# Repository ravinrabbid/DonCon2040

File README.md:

# DonCon2040 - A RP2040 based Taiko no Tatsujin arcade controller

DonCon2040 is a firmware (and by extension a PCB) for DIY Taiko no Tatsujin arcade style drum controllers.

It is pretty much tailored to this specific use case, if you are looking for something universal, ready-to-flash and on-the-fly configurable I'd recommend to have a look at more generic approaches like [GP2040-CE](https://github.com/OpenStickCommunity/GP2040-CE). If you however want build something more specialized or custom, feel free to use this project as a base, it is designed to be somewhat modular and should be easy remodel. See [DivaCon2040](https://github.com/ravinrabbid/DivaCon2040) for an example on how this could look like.
If you have any questions about the project in general or need hints how to build this thing, feel free to open a [discussion](https://github.com/ravinrabbid/DonCon2040/discussions) anytime!

## Features

- Various controller emulations
  - HORI PS4-095 Taiko Drum for Playstation 4 (will work on PS4, see [PS4 Authentication](#ps4-authentication) for details)
  - HORI NSW-079 Taiko Drum for Switch (compatible with Taiko no Tatsujin Rhythm Festival / Drum'n'Fun on Switch)
  - Bandai NC-110 Taiko Drum for Wii (needs to be connected to Wii Remote, see [Wii Support](#wii-support))
  - Namco NPC-107 Taiko Drum for Playstation 2 (needs to be connected to PS2 controller port, see [PS2 Support](#ps2-support))
  - Dualshock 4 (Only for PC/Steam, will not work on an actual PS4!)
  - Dualshock 3
  - Switch Pro Controller
  - XInput
  - XInput Analog (Compatible with [TaikoArcadeLoader](https://github.com/esuo1198/TaikoArcadeLoader) analog input)
  - Keyboard (Mapping: 'DFJK' / 'CBN,')
  - MIDI
  - Debug mode (will output current state via USB serial and allow direct flashing)
- Additional buttons via external i2c GPIO expander
- Basic configuration via on-screen menu on attached OLED screen
- Single WS2812 LED for trigger feedback
- Drumroll counter on display

## Building

I highly recommend to build the firmware yourself so you can make adjustments in `include/GlobalConfiguration.h` to match your specific controller build.
You can still use the [binary release](https://github.com/ravinrabbid/DonCon2040/releases) which is pre-configured for the [DonConIO](/pcb/DonConIO).

### VSCode (Windows, Linux, MacOS)

Install [VSCode](https://code.visualstudio.com/) and get the [Raspberry Pi Pico](https://marketplace.visualstudio.com/items?itemName=raspberry-pi.raspberry-pi-pico) extension. From the extension choose 'Import Project' and select the folder where you've checked out this repository, then use 'Compile Project'.

### CLI

See [pico-sdk readme](https://github.com/raspberrypi/pico-sdk/blob/master/README.md#quick-start-your-own-project) for a list of pre-requisites.

Use the environment variables `PICO_SDK_PATH` to use a local pico-sdk, and `PICO_BOARD` to select another target board.
By default the pico-sdk will be fetched from Github and the target board will be "pico".

For DonConIOmini with RP2040:

```sh
cmake -B build -DPICO_BOARD="waveshare_rp2040_zero"
cmake --build build
```

For DonConIOmini with RP2350:

```sh
cmake -B build -DPICO_BOARD="waveshare_rp2350_zero"
cmake --build build
```

For legacy DonConIO:

```sh
cmake -B build -DPICO_BOARD="seeed_xiao_rp2040"
cmake --build build
```

## Configuration

Few things which you probably want to change more regularly can be changed using an on-screen menu on the attached OLED display, hold both Start and Select for 2 seconds to enter the menu:

- Controller emulation mode
- LED brightness
- Trigger thresholds
- Hold Time
- Double Trigger Mode and Thresholds
- Enter BOOTSEL mode for firmware flashing

Those settings are persisted to flash memory if you choose 'Save' when exiting the Menu and will survive power cycles.

Defaults and everything else are compiled statically into the firmware. You can find everything in `include/GlobalConfiguration.h`. This covers default controller emulation mode, i2c pins, external ADC configuration, addresses and speed, default trigger thresholds, scale and debounce delay, button mapping, LED colors and brightness.

### Debounce Delay / Hold Time

The debounce delay also implicitly serves as the hold time of the input after a hit. On some platforms inputs won't be registered properly if this time is too short. For example Taiko no Tatsujin on Switch needs at least 25 milliseconds.

If you notice dropped inputs even if the controller signals a hit on the LED/Display, try to increase this value.

### Double Trigger (Large Notes)

Home versions of Taiko no Tatsujin give higher scores for large notes when both sides are hit simultaneously. In contrast, arcade versions will only need a normal hit (or sometimes a harder hit). To emulate this behavior, the following modes are offered:

- **Off**: Hit both sides to score large notes.
- **Threshold**: Automatically trigger both sides if a hit is stronger than the configured double hit threshold.
- **Always**: A hit on one side will always trigger the other side as well.

### PS4 Authentication

The PS4 needs a controller to sign a cryptographic challenge every few seconds, otherwise it will stop working after around 8 minutes after plugging in. For the Taiko no Tatsujin games this is somewhat bearable, since you can re-plug the controller before starting each song to avoid running into the timeout during gameplay. Still, this is annoying.

DonCon2040 can sign those challenges, but you will need to obtain some data from an original DS4 and compile it into the firmware. You will need a serial, signature and private key file. I can't and won't help you how to obtain those, you'll need to figure this out yourself.

To build the firmware run `scripts/generateAuthConfig.py` in the folder where you placed the required files. Copy the resulting `PS4AuthConfiguration.h` to the `include` directory, replacing the existing header. Then build the firmware as described in [Building](#building).

Signing the challenge will block the second core of the RP2040 for 2-3 seconds, so the display, external controller and LED will appear stuck from time to time. Input handling of the drum is unaffected.
On the RP2350 SHA256 is hardware accelerated, so signing time is reduced to about 1 second.

### Wii Support

To use the DonCon2040 with the Wii, it needs to be connected to the Wii Remote's extension port. This is only supported on boards exposing two I²C interfaces (i.e. the Waveshare RP2040/RP2350-Zero on the DonConIOmini).

See [the consolemods.org wiki](https://consolemods.org/wiki/Wii:Connector_Pinouts#Wii_Remote_Extension_Controller) for the pinout of the Wii Remote expansion port.
In the default configuration connect *SDA* to pin 0 and *SCL* to pin 1 of the RP2040/RP2350-Zero. Bridge *Sense* and *VCC* of the Wii Remote.

Since the Wii Remote is battery powered and the DonCon2040 needs to be powered externally because the Wii Remote does not provide enough power on the extension port,
I highly recommend to isolate the I²C bus (e.g. using an ISO1540 or ISO1640 I²C isolator).
While it does work when connecting the I²C signals directly, there is no guarantee there won't be any damage to the Wii Remote, its batteries or the DonCon2040 in the long run.
At least **DO NOT** connect both *VCC*s to avoid feeding power to the Wii Remote through the expansion port directly.

There is no dedicated mode for Wii support, it will be active in addition to the USB mode if `proprietary_device_config` is configured for Wii in `include/GlobalConfiguration.h`.

### PS2 Support

To use the DonCon2040 with the PS2, it needs to be connected to the PS2's controller port. This needs five consecutive GPIO pins on the RP2040/RP2350. The DonCon2040 still needs to be powered externally.

See [the consolemods.org wiki](https://consolemods.org/wiki/PS1:Connector_Pinouts#Controller_and_memory_card) for the pinout of the PS2 controller port.
The order of the signals lines is: Data, Command, Attention, Clock, Acknowledge.
In the default configuration, the base GPIO pin is 4, so the connection is as follows:

```txt
PS2 Controller Port     DonCon2040
----------------------------------
[1] (Data)          <-- GPIO4
[2] (Command)       --> GPIO5
[3] -
[4] GND             --- GND
[5] -
[6] (Attention)     --> GPIO6
[7] (Clock)         --> GPIO7
[8] -
[9] (Attention)     <-- GPIO8
```

There is no dedicated mode for PS2 support, it will be active in addition to the USB mode if `proprietary_device_config` is configured for PS2 in `include/GlobalConfiguration.h`.

## Hardware

### IO Board

The [DonConIOmini](/pcb/DonConIOmini) board in the pcb subfolder is designed to be close to the original arcade hardware. It hosts a Waveshare RP2040-Zero and provides signal conditioning for Sensatec GSS-4S* piezo impact sensors. See its [README](/pcb/DonConIOmini/README.md) for details.

If you don't want to use this board, the firmware should be usable on most RP2040/RP2350 boards with appropriate configuration. You may also use a more simple trigger solution, it only has to provide an analog trigger level to the ADC inputs to be compatible.

### Controller Buttons and Display

Additional controller buttons and the display are attached to the same (or different if your board has more than one) i2c bus. For the display, use a standard SSD1306 OLED display with 128x64 resolution. The buttons need to be attached to a MCP23017 IO expander.

See [DonConPad](/pcb/DonConPad/) for a exemplary gamepad pcb.

Mind that currently the display and buttons are mandatory to use the controller.

### Physical construction

I'll only give a rough outline of the physical construction since I'm still not completely happy with its performance and I'm still experimenting with some alternatives:

- The pads are made of 12mm thick multiplex boards. The outer diameter is ~42cm, the inner diameter is ~35cm.
- Pads are mounted to another 20mm multiplex board with rubber dampeners. The backplates on the arcade drum seem to be thinner, but since those are sturdily mounted to the arcade machine, I figured some more mass couldn't hurt.
- The rubber dampeners are 15mm of height and 20mm in diameter. The arcade drum seems to use tapered dampeners, but at least the tapered dampeners I could get my hands on felt too soft, so I went with straight ones.
- For the drum skin I tried with a 2mm natural rubber sheet covered by some canvas, which worked reasonably well but is pretty loud and has little rebound. I imported real arcade drum skins now, which work a lot better.

## Acknowledgements

- [daschr](https://github.com/daschr) for the [SSD1306 OLED driver](https://github.com/daschr/pico-ssd1306)
- [FeralAI](https://github.com/FeralAI) for the inspiration and Dualshock3/XInput driver from the [GP2040 Project](https://github.com/FeralAI/GP2040)
- The linux kernel contributors for documenting the game controllers in their drivers

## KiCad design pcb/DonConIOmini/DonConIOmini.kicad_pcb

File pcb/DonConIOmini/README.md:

# DonConIOmini - Signal Conditioning for the DonCon2040

This board hosts a Waveshare RP2040-Zero or RP2350-Zero microcontroller unit and provides signal conditioning for the piezo drum triggers. The conditioning circuit is reverse engineered from the *V260 SIF PCB* found in the original arcades. In contrast to the original [DonConIO](/pcb/DonConIO) this board uses mainly SMD parts... less authentic but way better noise characteristics.

## Sensors

The arcade drum uses *Sensatec GSS-4SD* piezo impact sensors. While those are only available as expensive arcade spare parts, the *GSS-4SA* and *GSS-4SC* variants used in this build can be readily ordered directly from the manufacturer. My guess here is that the *D* variant only uses a different cable and connector, but who knows ...

You can also try your luck with any generic piezo, in this case you might have to tune the filters and amplification factor.

## Notes

- If the sensitivity for a pad feels to low you can try to increase the feedback resistor (R3,R13,R21,R30) of the affected pad for more amplification.
- You might also get better sensitivity using larger (2.2nF) capacitors for C1,C3,C5 and C7 depending on your drum construction.
- This board does not use the internal ADCs of the RP2040 since those are pretty noisy and have a static offset of around +25mV. You can however still skip the external ADC and level-shifter and connect the signals directly to ADC pins of the RP2040-Zero if you want to save some cost.

## Bill of Materials

| **Reference**                                         |                   **Description**                    |     **Digikey Part**      |                  **Notes**                   |
| ----------------------------------------------------- | :--------------------------------------------------: | :-----------------------: | :------------------------------------------: |
| U3                                                    |    Waveshare RP2040-Zero or Waveshare RP2350-Zero    |             -             |                                              |
| U1, U2                                                |                 TL072CDR JFET OpAmp                  |       296-1283-1-ND       |                                              |
| U5                                                    |                MCP3204 12bit SPI ADC                 |     MCP3204-CI/SL-ND      |                                              |
| U6                                                    |           MCP1541 4.09V Voltage Reference            |    MCP1541T-I/TTCT-ND     |                                              |
| U7                                                    | TXB0104 4-Bit Bidirectional Voltage-Level Translator |      296-21928-1-ND       |                                              |
| PS1                                                   |              +/-12V DC to DC Converter               |        811-3205-ND        |                                              |
| C1, C3, C5, C7                                        |                  1nF Film Capacitor                  |       399-11751-ND        |                                              |
| C2, C4, C6, C8                                        |            0.47µF SMD Tantalum Capacitor             |       399-8287-1-ND       |                                              |
| C9, C10, C13, C14, C20, C22, C24, C25                 |             0.1µF SMD Ceramic Capacitor              |      1276-1003-1-ND       |                                              |
| C17                                                   |             4.7µF Electrolytic Capacitor             |     50YXJ4.7M5X11-ND      |                                              |
| C18, C19                                              |              1µF Electrolytic Capacitor              |       1189-1421-ND        |                                              |
| C21                                                   |              10µF SMD Ceramic Capacitor              |      1276-6454-1-ND       |                                              |
| D1, D2, D5, D7, D8, D11, D13, D14, D17, D19, D20, D23 |                  1N4148WS SMD Diode                  |     1N4148WS-FDICT-ND     |                                              |
| D3, D4, D9, D10, D15, D16, D21, D22                   |               BAT43 SMD Schottky Diode               |  112-BAT43WS-E3-08CT-ND   |        1N4148 will probably work too         |
| D6, D12, D18, D24                                     |              4.3V 400mW SMD Zener Diode              |    1727-PDZ4.3BZCT-ND     |                                              |
| R1, R10, R19, R28                                     |                   1MΩ SMD Resistor                   | 2019-RK73H2ATTD1004FCT-ND |                                              |
| R2, R11, R20, R29                                     |                  4.7kΩ SMD Resistor                  | 2019-RK73H2ATTD4701FCT-ND |                                              |
| R3, R12, R21, R30                                     |                  100kΩ SMD Resistor                  | 2019-RK73H2ATTD1003FCT-ND |                                              |
| R4, R13, R22, R31                                     |                  100Ω SMD Resistor                   | 2019-RK73H2ATTD1000FCT-ND |                                              |
| R6, R15, R24, R33                                     |                  5.1kΩ SMD Resistor                  | 2019-RK73H2ATTD5101FCT-ND |                                              |
| R7, R16, R25, R34, R37                                |                  10kΩ SMD Resistor                   | 2019-RK73H2ATTD1002FCT-ND |                                              |
| R8, R17, R26, R35                                     |                   1kΩ SMD Resistor                   | 2019-RK73H2ATTD1001FCT-ND |                                              |
| R9, R18, R27, R36                                     |                  300Ω SMD Resistor                   | 2019-RK73H2ATTD3000FCT-ND |                                              |
| J1, J2, J3, J4                                        |              2Pin S2B-PH-K-S Connector               |        455-1719-ND        | PHR-2 plus SPH-002T-P0.5L is the counterpart |
| J5                                                    |              5Pin S5B-PH-K-S Connector               |        455-1722-ND        | PHR-5 plus SPH-002T-P0.5L is the counterpart |

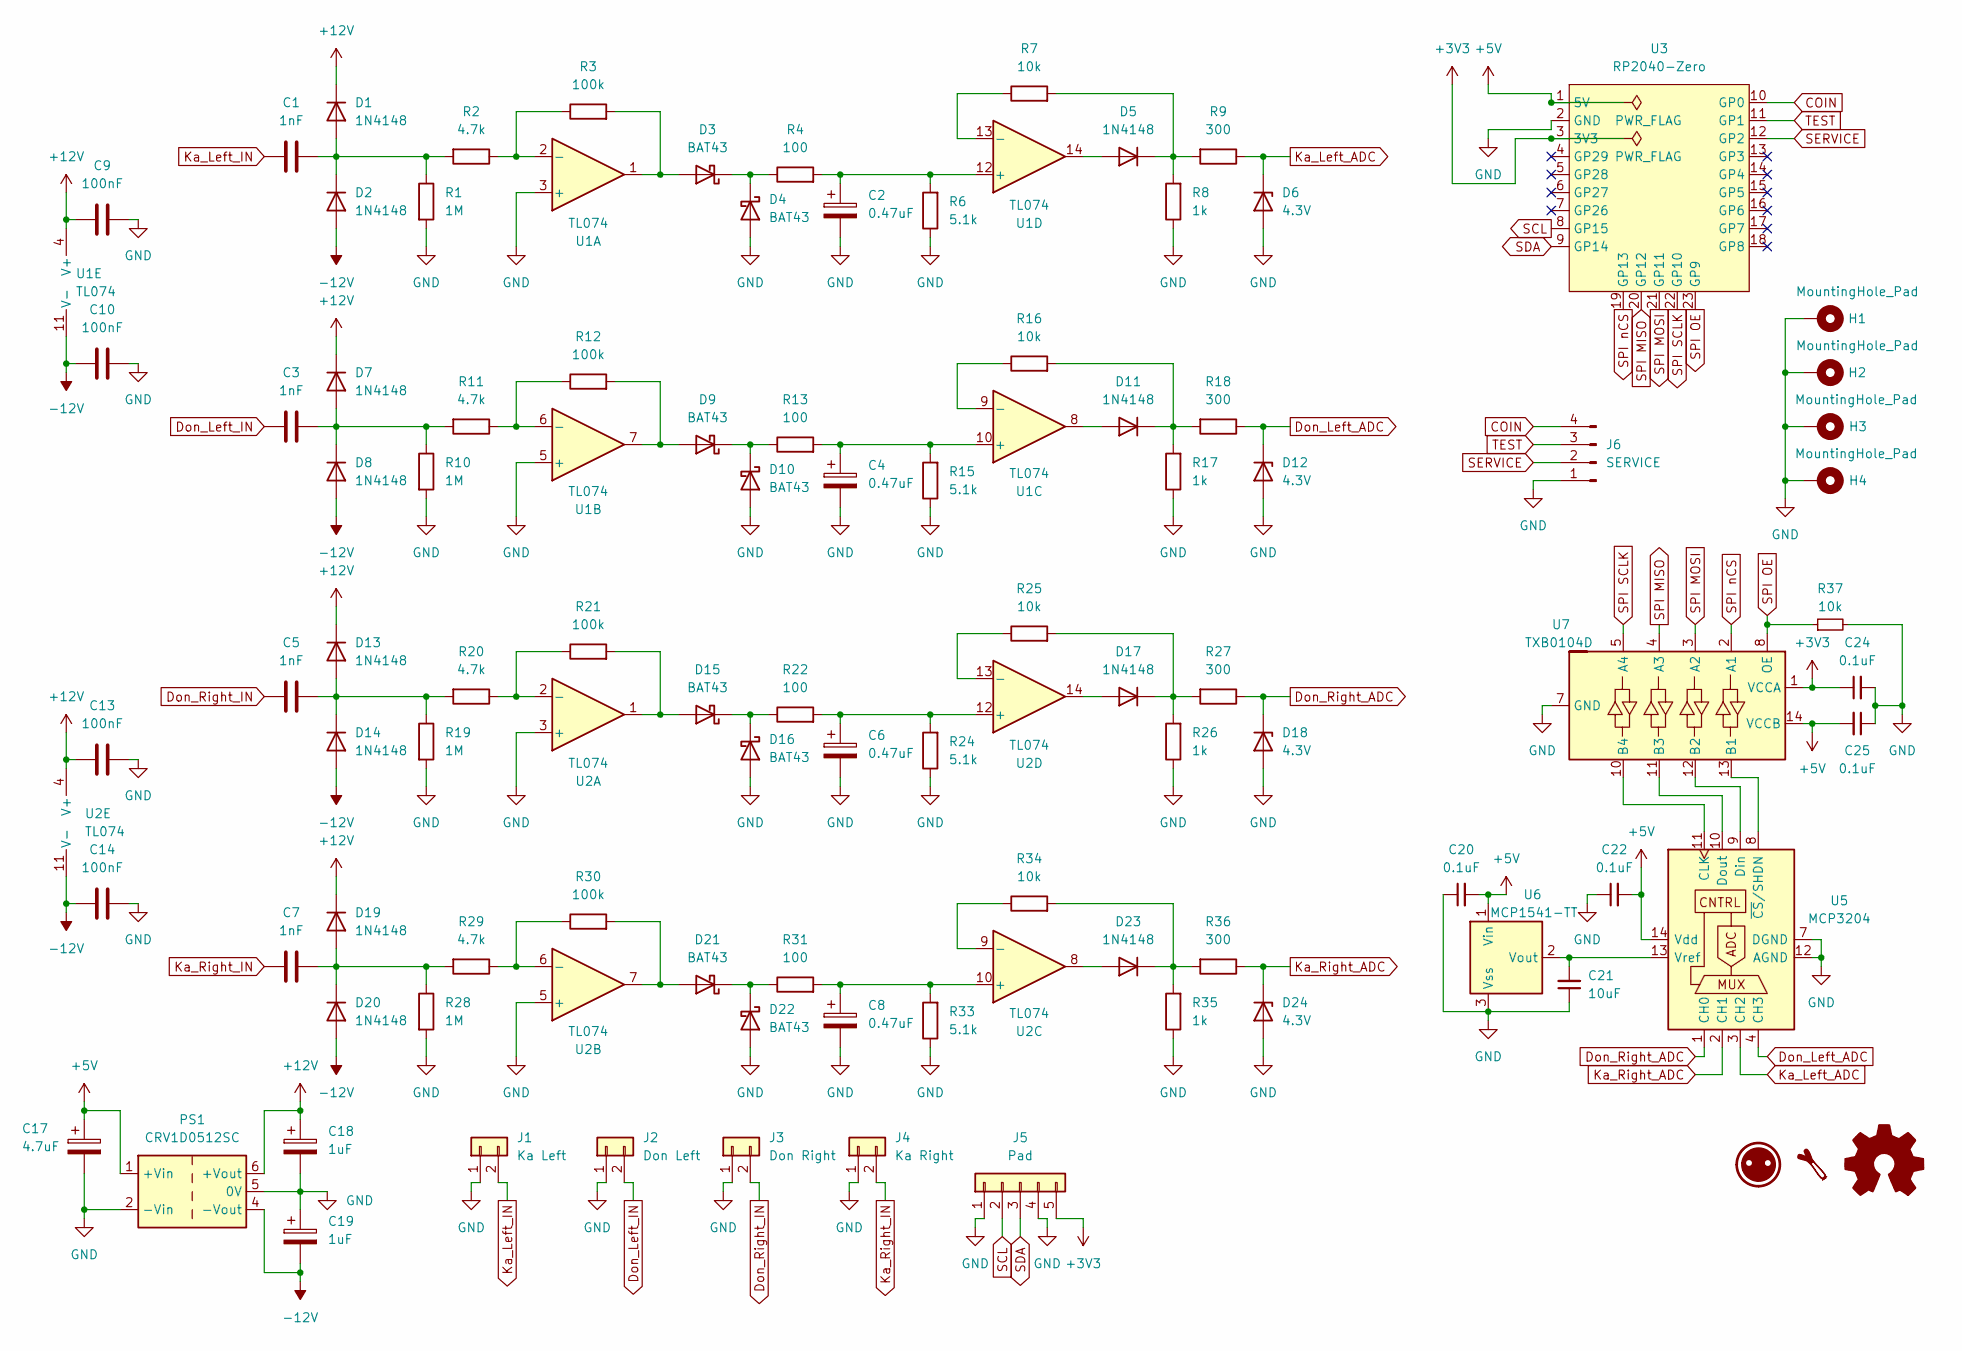
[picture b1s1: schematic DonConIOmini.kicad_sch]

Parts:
C1, C3, C5, C7: 1nF; C_Rect_L7.2mm_W2.5mm_P5.00mm_FKS2_FKP2_MKS2_MKP2
C2, C4, C6, C8: 0.47uF; C_1206_3216Metric_Pad1.33x1.80mm_HandSolder
C9, C10, C13, C14: 100nF; C_0805_2012Metric_Pad1.18x1.45mm_HandSolder
C17: 4.7uF; CP_Radial_D5.0mm_P2.00mm
C18, C19: 1uF; CP_Radial_D5.0mm_P2.00mm
C20, C22, C24, C25: 0.1uF; C_0805_2012Metric_Pad1.18x1.45mm_HandSolder
C21: 10uF; C_0805_2012Metric_Pad1.18x1.45mm_HandSolder
D1, D2, D5, D7, D8, D11, D13, D14, D17, D19, D20, D23: 1N4148; D_SOD-323_HandSoldering
D3, D4, D9, D10, D15, D16, D21, D22: BAT43; D_SOD-323_HandSoldering
D6, D12, D18, D24: 4.3V; D_SOD-323_HandSoldering
H1, H2, H3, H4: MountingHole_Pad; MountingHole_4.5mm_Pad_TopOnly
J1: Ka Left; JST_PH_S2B-PH-K_1x02_P2.00mm_Horizontal
J2: Don Left; JST_PH_S2B-PH-K_1x02_P2.00mm_Horizontal
J3: Don Right; JST_PH_S2B-PH-K_1x02_P2.00mm_Horizontal
J4: Ka Right; JST_PH_S2B-PH-K_1x02_P2.00mm_Horizontal
J5: Pad; JST_PH_S5B-PH-K_1x05_P2.00mm_Horizontal
J6: SERVICE; JST_XH_S4B-XH-A_1x04_P2.50mm_Horizontal
PS1: CRV1D0512SC; CRV1DxxxSC
R1, R10, R19, R28: 1M; R_0805_2012Metric_Pad1.20x1.40mm_HandSolder
R2, R11, R20, R29: 4.7k; R_0805_2012Metric_Pad1.20x1.40mm_HandSolder
R3, R12, R21, R30: 100k; R_0805_2012Metric_Pad1.20x1.40mm_HandSolder
R4, R13, R22, R31: 100; R_0805_2012Metric_Pad1.20x1.40mm_HandSolder
R6, R15, R24, R33: 5.1k; R_0805_2012Metric_Pad1.20x1.40mm_HandSolder
R7, R16, R25, R34, R37: 10k; R_0805_2012Metric_Pad1.20x1.40mm_HandSolder
R8, R17, R26, R35: 1k; R_0805_2012Metric_Pad1.20x1.40mm_HandSolder
R9, R18, R27, R36: 300; R_0805_2012Metric_Pad1.20x1.40mm_HandSolder
U1, U2: TL074; SOIC-14_3.9x8.7mm_P1.27mm
U3: RP2040-Zero; RP2040 Zero
U5: MCP3204; SOIC-14_3.9x8.7mm_P1.27mm
U6: MCP1541-TT; SOT-23
U7: TXB0104D; SOIC-14_3.9x8.7mm_P1.27mm

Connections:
+3V3: C24.1, J5.5, U3.3 (3V3), U7.1 (VCCA)
+5V: C17.1, C20.2, C22.2, C25.2, PS1.1 (+Vin), U3.1 (5V), U5.14 (Vdd), U6.1 (Vin), U7.14 (VCCB)
+12V: C9.1, C13.1, C18.1, D1.1 (K), D7.1 (K), D13.1 (K), D19.1 (K), PS1.6 (+Vout), U1.4 (V+), U2.4 (V+)
-12V: C10.1, C14.1, C19.2, D2.2 (A), D8.2 (A), D14.2 (A), D20.2 (A), PS1.4 (-Vout), U1.11 (V-), U2.11 (V-)
COIN: J6.4, U3.10 (GP0)
Don_Left_ADC: D12.1 (K), R18.1, U5.4 (CH3)
Don_Left_IN: C3.1, J2.2
Don_Right_ADC: D18.1 (K), R27.1, U5.1 (CH0)
Don_Right_IN: C5.1, J3.2
GND: C2.2, C4.2, C6.2, C8.2, C9.2, C10.2, C13.2, C14.2, C17.2, C18.2, C19.1, C20.1, C21.1, C22.1, C24.2, C25.1, D4.2 (A), D6.2 (A), D10.2 (A), D12.2 (A), D16.2 (A), D18.2 (A), D22.2 (A), D24.2 (A), H1.1, H2.1, H3.1, H4.1, J1.1, J2.1, J3.1, J4.1, J5.1, J5.4, J6.1, PS1.2 (-Vin), PS1.5 (0V), R1.2, R6.1, R8.1, R10.2, R15.1, R17.1, R19.2, R24.1, R26.1, R28.2, R33.1, R35.1, R37.2, U1.3 (+), U1.5 (+), U2.3 (+), U2.5 (+), U3.2 (GND), U5.7 (DGND), U5.12 (AGND), U6.3 (Vss), U7.7 (GND)
Ka_Left_ADC: D6.1 (K), R9.1, U5.3 (CH2)
Ka_Left_IN: C1.1, J1.2
Ka_Right_ADC: D24.1 (K), R36.1, U5.2 (CH1)
Ka_Right_IN: C7.1, J4.2
unnamed: C1.2, D1.2 (A), D2.1 (K), R1.1, R2.2
unnamed: D3.2 (A), R3.2, U1.1
unnamed: D3.1 (K), D4.1 (K), R4.1
unnamed: D5.2 (A), U1.14
unnamed: D5.1 (K), R7.2, R8.2, R9.2
unnamed: C3.2, D7.2 (A), D8.1 (K), R10.1, R11.2
unnamed: D9.2 (A), R12.2, U1.7
unnamed: D9.1 (K), D10.1 (K), R13.1
unnamed: D11.2 (A), U1.8
unnamed: D11.1 (K), R16.2, R17.2, R18.2
unnamed: C5.2, D13.2 (A), D14.1 (K), R19.1, R20.2
unnamed: D15.2 (A), R21.2, U2.1
unnamed: D15.1 (K), D16.1 (K), R22.1
unnamed: D17.2 (A), U2.14
unnamed: D17.1 (K), R25.2, R26.2, R27.2
unnamed: C7.2, D19.2 (A), D20.1 (K), R28.1, R29.2
unnamed: D21.2 (A), R30.2, U2.7
unnamed: D21.1 (K), D22.1 (K), R31.1
unnamed: D23.2 (A), U2.8
unnamed: D23.1 (K), R34.2, R35.2, R36.2
unnamed: R2.1, R3.1, U1.2 (-)
unnamed: R11.1, R12.1, U1.6 (-)
unnamed: C4.1, R13.2, R15.2, U1.10 (+)
unnamed: R16.1, U1.9 (-)
unnamed: C2.1, R4.2, R6.2, U1.12 (+)
unnamed: R7.1, U1.13 (-)
unnamed: R20.1, R21.1, U2.2 (-)
unnamed: R29.1, R30.1, U2.6 (-)
unnamed: C8.1, R31.2, R33.2, U2.10 (+)
unnamed: R34.1, U2.9 (-)
unnamed: C6.1, R22.2, R24.2, U2.12 (+)
unnamed: R25.1, U2.13 (-)
unnamed: U5.11 (CLK), U7.10 (B4)
unnamed: U5.9 (Din), U7.12 (B2)
unnamed: U5.10 (Dout), U7.11 (B3)
unnamed: C21.2, U5.13 (Vref), U6.2 (Vout)
unnamed: U5.8 (~CS/SHDN), U7.13 (B1)
SCL: J5.2, U3.8 (GP15)
SDA: J5.3, U3.9 (GP14)
SERVICE: J6.2, U3.12 (GP2)
SPI MISO: U3.20 (GP12), U7.4 (A3)
SPI MOSI: U3.21 (GP11), U7.3 (A2)
SPI OE: R37.1, U3.23 (GP9), U7.8 (OE)
SPI SCLK: U3.22 (GP10), U7.5 (A4)
SPI nCS: U3.19 (GP13), U7.2 (A1)
TEST: J6.3, U3.11 (GP1)

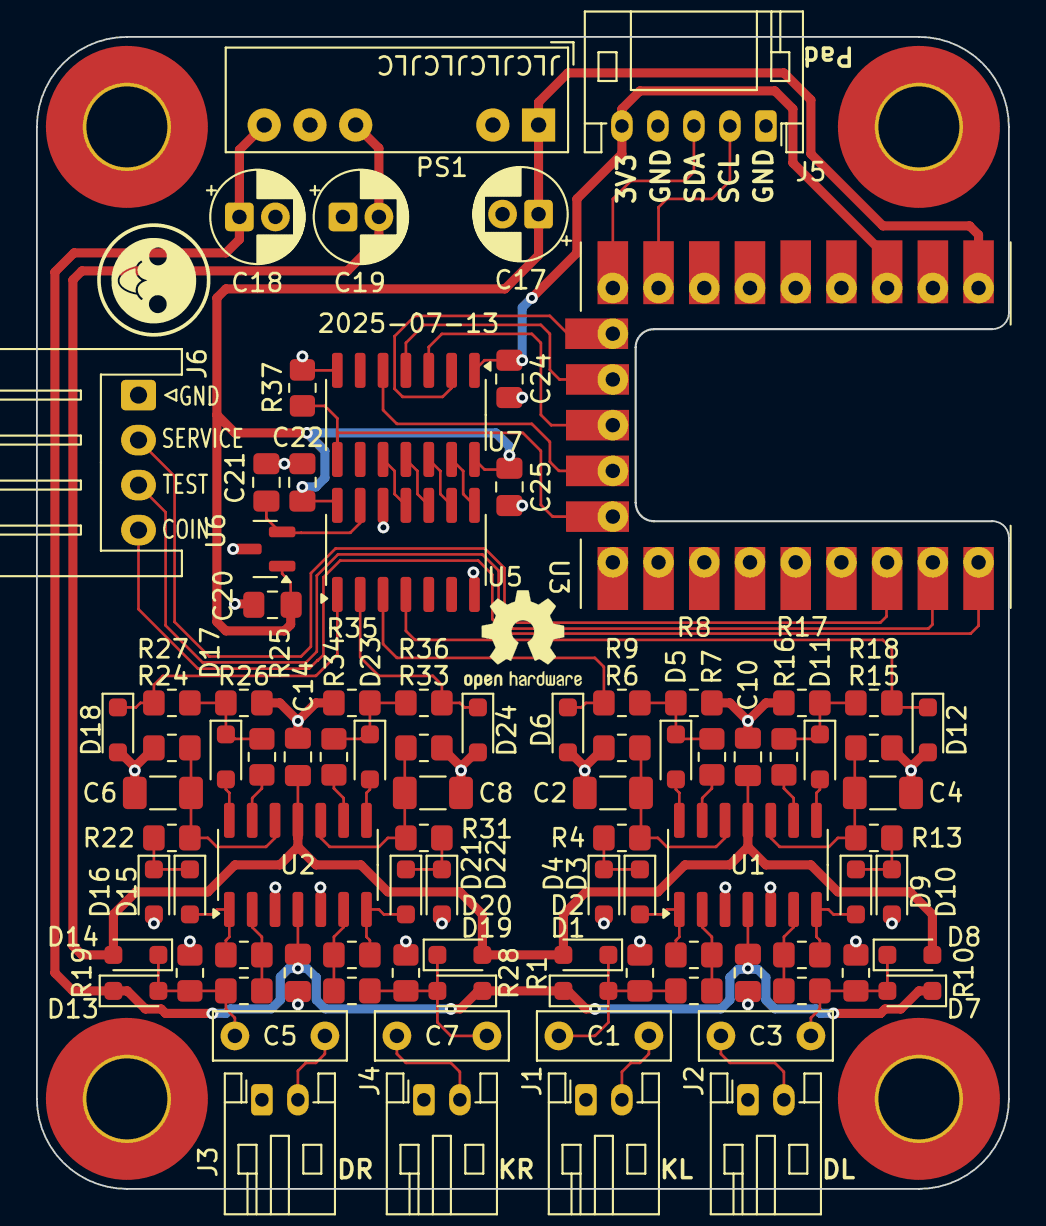
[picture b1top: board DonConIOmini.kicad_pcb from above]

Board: 2 copper layers, 54.0 x 64.0 mm, 96 parts (0 on the bottom side), 60 nets.

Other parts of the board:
REF01: OSHW-Logo2_7.3x6mm_SilkScreen
REF02: Donchan-Logo_6.3mm_Silkscreen

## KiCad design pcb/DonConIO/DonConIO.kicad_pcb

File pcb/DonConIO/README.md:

# DonConIO - Signal Conditioning for the DonCon2040

---

## NOTICE

**DEPRECATED.**

While this board will still work fine, I recommend using the [DonConIOmini](/pcb/DonConIOmini). It hosts the same circuit using mainly SMD parts, resulting in a smaller footprint and better noise characteristics.

---

This board hosts a Seeed Studio XIAO RP2040 microcontroller unit and provides signal conditioning for the piezo drum triggers. The conditioning circuit is reverse engineered from the *V260 SIF PCB* found in the original arcades. This is also the main reason why this board uses mainly through hole parts ... for *authenticity*.

## Sensors

The arcade drum uses *Sensatec GSS-4SD* piezo impact sensors. While those are only available as expensive arcade spare parts, the *GSS-4SA* and *GSS-4SC* variants used in this build can be readily ordered directly from the manufacturer. My guess here is that the *D* variant only uses a different cable and connector, but who knows ...

You can also try your luck with any generic piezo, in this case you might have to tune the filters and amplification factor.

## Notes

- If the sensitivity for a pad feels to low you can try to increase the feedback resistor (R3,R13,R21,R30) of the affected pad for more amplification.
- This board does not use the internal ADCs of the RP2040 since those are pretty noisy and have a static offset of around +25mV. You can however still skip the external ADC and level-shifter and connect the signals directly to ADC pins of the XIAO RP2040 if you want to save some cost.

## Bill of Materials

| **Reference**                                         |                   **Description**                    |     **Digikey Part**      |                                         **Notes**                                         |
| ----------------------------------------------------- | :--------------------------------------------------: | :-----------------------: | :---------------------------------------------------------------------------------------: |
| J6, J7                                                |               Seeed Studio XIAO RP2040               |             -             |                                                                                           |
| U1, U2, U3, U4                                        |                  TL072CP JFET OpAmp                  |       296-1775-5-ND       |                                                                                           |
| U5                                                    |                MCP3204 12bit SPI ADC                 |     MCP3204-CI/SL-ND      |                                                                                           |
| U6                                                    |           MCP1541 4.09V Voltage Reference            |    MCP1541T-I/TTCT-ND     |                                                                                           |
| U7                                                    | TXB0104 4-Bit Bidirectional Voltage-Level Translator |      296-21928-1-ND       |                                                                                           |
| PS1                                                   |              +/-12V DC to DC Converter               |    2725-A0512S-1WR3-ND    |                                                                                           |
| C1, C3, C5, C7                                        |            1nF Mylar/Polyester Capacitor             |       493-14299-ND        |                                                                                           |
| C2, C4, C6, C8                                        |              0.47µF Tantalum Capacitor               |        478-1901-ND        |                                                                                           |
| C9-C16                                                |               100nF Ceramic Capacitor                |        BC1084CT-ND        |                                                                                           |
| C17                                                   |             4.7µF Electrolytic Capacitor             |       1189-1421-ND        |                                                                                           |
| C18, C19                                              |              1µF Electrolytic Capacitor              |     50YXJ4.7M5X11-ND      |                                                                                           |
| C20, C22, C24, C25                                    |             0.1µF SMD Ceramic Capacitor              |      1276-1003-1-ND       |                                                                                           |
| C21, C23, C26                                         |              10µF SMD Ceramic Capacitor              |      1276-6454-1-ND       |                                                                                           |
| D1, D2, D5, D7, D8, D11, D13, D14, D17, D19, D20, D23 |              1SS133M Small Signal Diode              |      1SS133MR0GCT-ND      | While the 1SS133M is probably more *authentic*, a 1N4148 will probably just work as well. |
| D3, D4, D9, D10, D15, D16, D21, D22                   |                 BAT43 Schottky Diode                 |    112-BAT43-TAPCT-ND     |                                                                                           |
| D6, D12, D18, D24                                     |            1N5229B 4.3V 500mW Zener Diode            |      1N5229BFSCT-ND       |                                                                                           |
| R1, R10, R19, R28                                     |                     1MΩ Resistor                     |  13-MFR-25FTE52-1MCT-ND   |                                                                                           |
| R2, R11, R20, R29                                     |                    4.7kΩ Resistor                    |  13-MFR-25FRF52-4K7CT-ND  |                                                                                           |
| R3, R12, R21, R30                                     |                    100kΩ Resistor                    | 13-MFR-25FRF52-100KCT-ND  |                                                                                           |
| R4, R13, R22, R31                                     |                    100Ω Resistor                     | 13-MFR-25FRF52-100RCT-ND  |                                                                                           |
| R6, R15, R24, R33                                     |                    5.1kΩ Resistor                    |  13-MFR-25FRF52-5K1CT-ND  |                                                                                           |
| R7, R16, R25, R34                                     |                    10kΩ Resistor                     |  13-MFR-25FRF52-10KCT-ND  |
| R8, R17, R26, R35                                     |                     1kΩ Resistor                     |  13-MFR-25FRF52-1KCT-ND   |
| R9, R18, R27, R36                                     |                    300Ω Resistor                     |     MFR-25FRF52-300R      |
| R37                                                   |                  10kΩ SMD Resistor                   | 2019-RK73H2ATTD1002FCT-ND |                                                                                           |
| J1, J2, J3, J4                                        |              2Pin S2B-PH-K-S Connector               |        455-1719-ND        |                       PHR-2 plus SPH-002T-P0.5L is the counterpart                        |
| J5                                                    |              5Pin S5B-PH-K-S Connector               |        455-1722-ND        |                       PHR-5 plus SPH-002T-P0.5L is the counterpart                        |

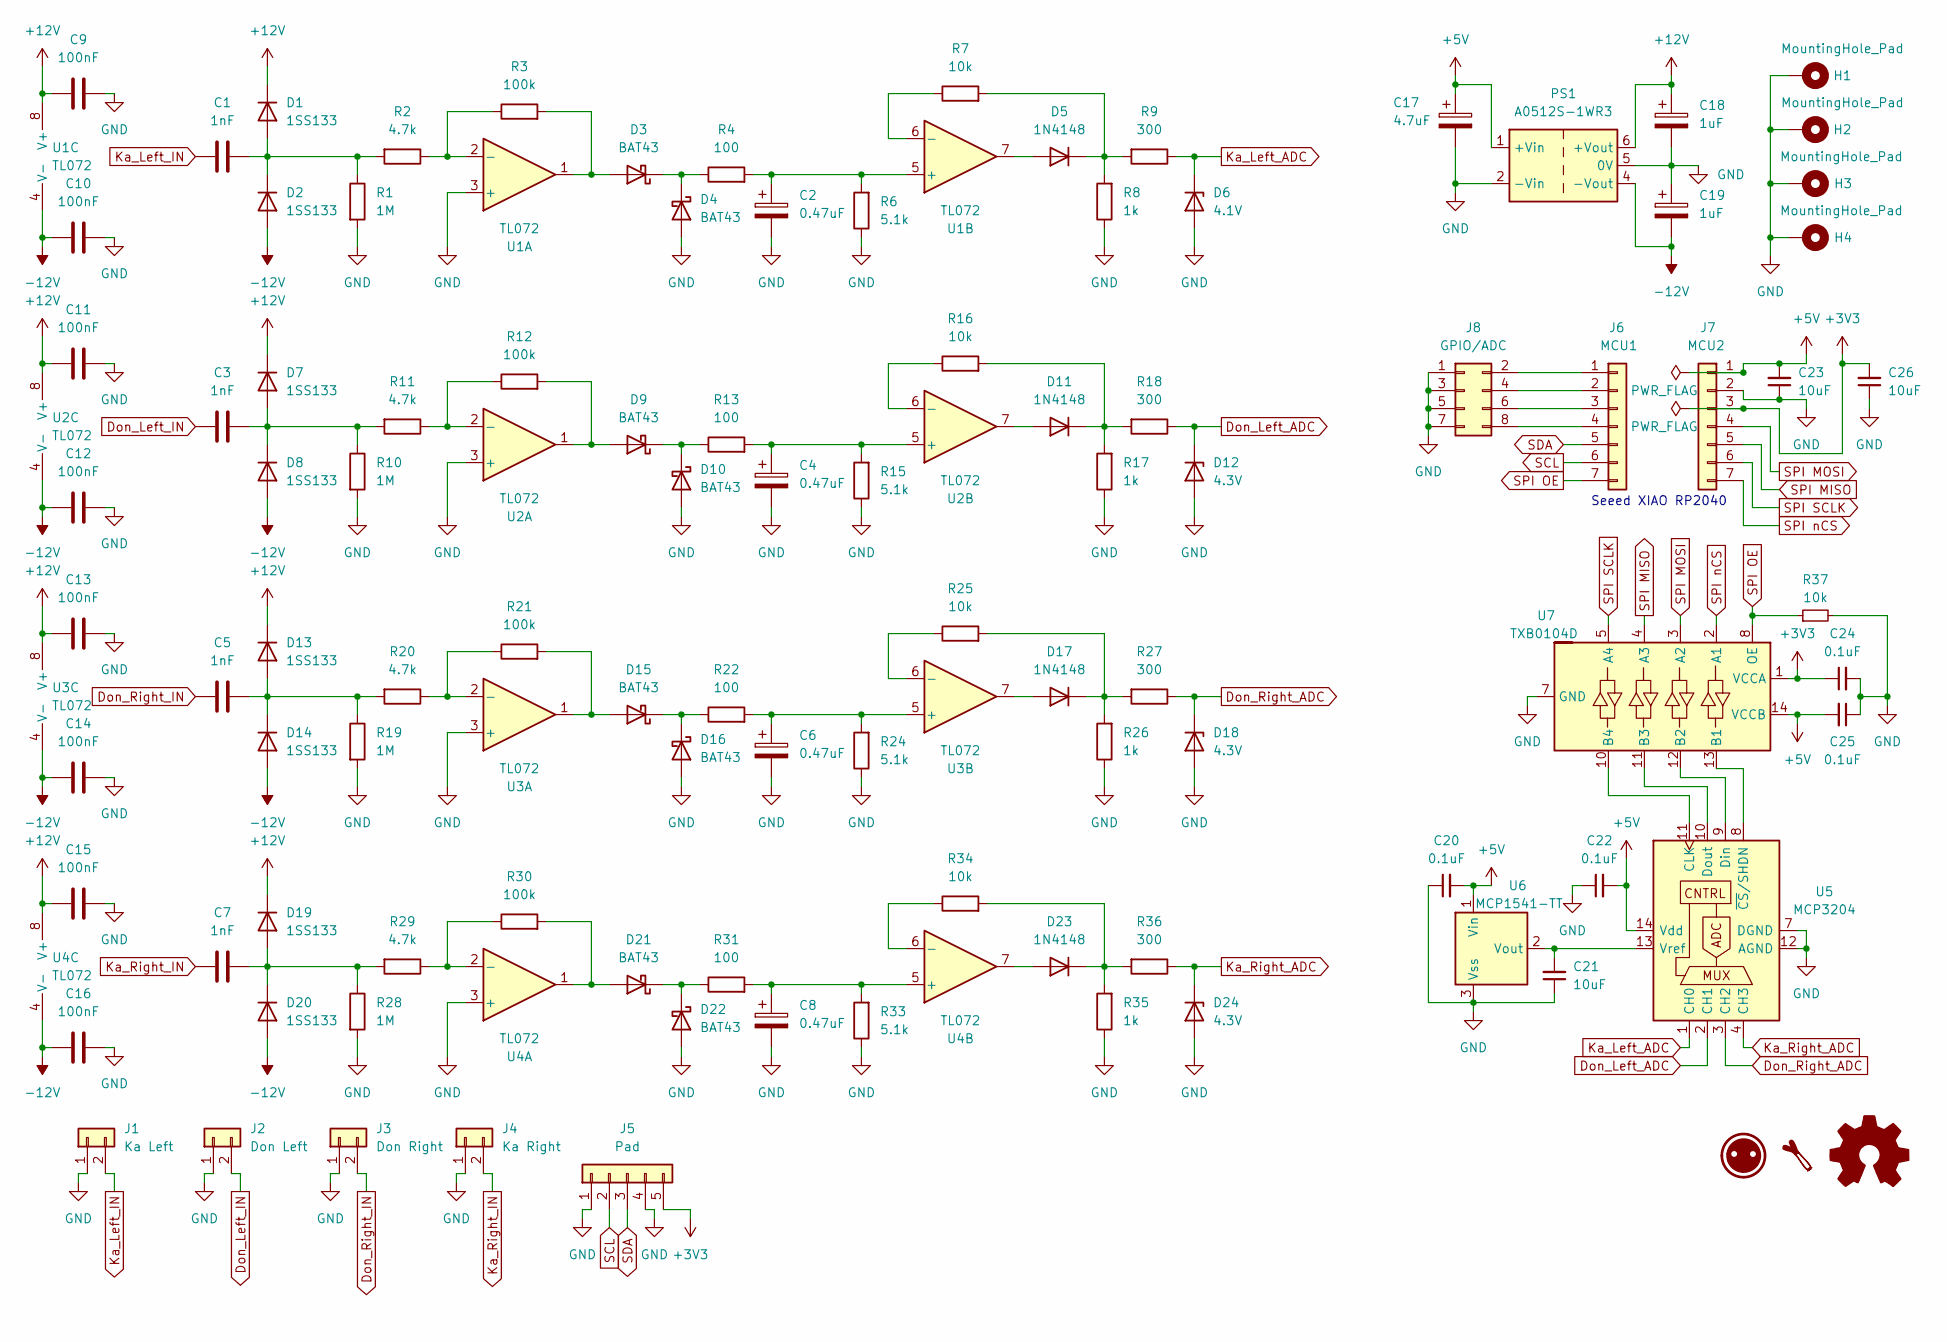
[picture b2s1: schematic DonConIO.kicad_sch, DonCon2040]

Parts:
C1, C3, C5, C7: 1nF; C_Rect_L7.0mm_W3.5mm_P5.00mm
C2, C4, C6, C8: 0.47uF; CP_Radial_Tantal_D4.5mm_P2.50mm
C9, C10, C11, C12, C13, C14, C15, C16: 100nF; C_Disc_D3.8mm_W2.6mm_P2.50mm
C17: 4.7uF; CP_Radial_D5.0mm_P2.00mm
C18, C19: 1uF; CP_Radial_D5.0mm_P2.00mm
C20, C22, C24, C25: 0.1uF; C_0805_2012Metric_Pad1.18x1.45mm_HandSolder
C21, C23, C26: 10uF; C_0805_2012Metric_Pad1.18x1.45mm_HandSolder
D1, D2, D7, D8, D13, D14, D19, D20: 1SS133; D_DO-35_SOD27_P7.62mm_Horizontal
D3, D4, D9, D10, D15, D16, D21, D22: BAT43; D_DO-35_SOD27_P7.62mm_Horizontal
D5, D11, D17, D23: 1N4148; D_DO-35_SOD27_P7.62mm_Horizontal
D6: 4.1V; D_DO-35_SOD27_P7.62mm_Horizontal
D12, D18, D24: 4.3V; D_DO-35_SOD27_P7.62mm_Horizontal
H1, H2, H3, H4: MountingHole_Pad; MountingHole_4.5mm_Pad_TopOnly
J1: Ka Left; JST_PH_S2B-PH-K_1x02_P2.00mm_Horizontal
J2: Don Left; JST_PH_S2B-PH-K_1x02_P2.00mm_Horizontal
J3: Don Right; JST_PH_S2B-PH-K_1x02_P2.00mm_Horizontal
J4: Ka Right; JST_PH_S2B-PH-K_1x02_P2.00mm_Horizontal
J5: Pad; JST_PH_S5B-PH-K_1x05_P2.00mm_Horizontal
J6: MCU1; PinSocket_1x07_P2.54mm_Vertical
J7: MCU2; PinSocket_1x07_P2.54mm_Vertical
J8: GPIO/ADC; PinHeader_2x04_P2.54mm_Vertical
PS1: A0512S-1WR3; Converter_DCDC_XP_POWER-IAxxxxS_THT
R1, R10, R19, R28: 1M; R_Axial_DIN0207_L6.3mm_D2.5mm_P7.62mm_Horizontal
R2, R11, R20, R29: 4.7k; R_Axial_DIN0207_L6.3mm_D2.5mm_P7.62mm_Horizontal
R3, R12, R21, R30: 100k; R_Axial_DIN0207_L6.3mm_D2.5mm_P7.62mm_Horizontal
R4, R13, R22, R31: 100; R_Axial_DIN0207_L6.3mm_D2.5mm_P7.62mm_Horizontal
R6, R15, R24, R33: 5.1k; R_Axial_DIN0207_L6.3mm_D2.5mm_P7.62mm_Horizontal
R7, R16, R25, R34: 10k; R_Axial_DIN0207_L6.3mm_D2.5mm_P7.62mm_Horizontal
R8, R17, R26, R35: 1k; R_Axial_DIN0207_L6.3mm_D2.5mm_P7.62mm_Horizontal
R9, R18, R27, R36: 300; R_Axial_DIN0207_L6.3mm_D2.5mm_P7.62mm_Horizontal
R37: 10k; R_0805_2012Metric_Pad1.20x1.40mm_HandSolder
U1, U2, U3, U4: TL072; DIP-8_W7.62mm_Socket
U5: MCP3204; SOIC-14_3.9x8.7mm_P1.27mm
U6: MCP1541-TT; SOT-23
U7: TXB0104D; SOIC-14_3.9x8.7mm_P1.27mm

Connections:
+3V3: C24.1, C26.2, J5.5, J7.3, U7.1 (VCCA)
+5V: C17.1, C20.2, C22.2, C23.2, C25.2, J7.1, PS1.1 (+Vin), U5.14 (Vdd), U6.1 (Vin), U7.14 (VCCB)
+12V: C9.1, C11.1, C13.1, C15.1, C18.1, D1.1 (K), D7.1 (K), D13.1 (K), D19.1 (K), PS1.6 (+Vout), U1.8 (V+), U2.8 (V+), U3.8 (V+), U4.8 (V+)
-12V: C10.1, C12.1, C14.1, C16.1, C19.2, D2.2 (A), D8.2 (A), D14.2 (A), D20.2 (A), PS1.4 (-Vout), U1.4 (V-), U2.4 (V-), U3.4 (V-), U4.4 (V-)
Don_Left_ADC: D12.1 (K), R18.1, U5.2 (CH1)
Don_Left_IN: C3.1, J2.2
Don_Right_ADC: D18.1 (K), R27.1, U5.3 (CH2)
Don_Right_IN: C5.1, J3.2
GND: C2.2, C4.2, C6.2, C8.2, C9.2, C10.2, C11.2, C12.2, C13.2, C14.2, C15.2, C16.2, C17.2, C18.2, C19.1, C20.1, C21.1, C22.1, C23.1, C24.2, C25.1, C26.1, D4.2 (A), D6.2 (A), D10.2 (A), D12.2 (A), D16.2 (A), D18.2 (A), D22.2 (A), D24.2 (A), H1.1, H2.1, H3.1, H4.1, J1.1, J2.1, J3.1, J4.1, J5.1, J5.4, J7.2, J8.1, J8.3, J8.5, J8.7, PS1.2 (-Vin), PS1.5 (0V), R1.2, R6.1, R8.1, R10.2, R15.1, R17.1, R19.2, R24.1, R26.1, R28.2, R33.1, R35.1, R37.2, U1.3 (+), U2.3 (+), U3.3 (+), U4.3 (+), U5.7 (DGND), U5.12 (AGND), U6.3 (Vss), U7.7 (GND)
Ka_Left_ADC: D6.1 (K), R9.1, U5.1 (CH0)
Ka_Left_IN: C1.1, J1.2
Ka_Right_ADC: D24.1 (K), R36.1, U5.4 (CH3)
Ka_Right_IN: C7.1, J4.2
unnamed: C1.2, D1.2 (A), D2.1 (K), R1.1, R2.2
unnamed: D3.2 (A), R3.2, U1.1
unnamed: D3.1 (K), D4.1 (K), R4.1
unnamed: D5.2 (A), U1.7
unnamed: D5.1 (K), R7.2, R8.2, R9.2
unnamed: C3.2, D7.2 (A), D8.1 (K), R10.1, R11.2
unnamed: D9.2 (A), R12.2, U2.1
unnamed: D9.1 (K), D10.1 (K), R13.1
unnamed: D11.2 (A), U2.7
unnamed: D11.1 (K), R16.2, R17.2, R18.2
unnamed: C5.2, D13.2 (A), D14.1 (K), R19.1, R20.2
unnamed: D15.2 (A), R21.2, U3.1
unnamed: D15.1 (K), D16.1 (K), R22.1
unnamed: D17.2 (A), U3.7
unnamed: D17.1 (K), R25.2, R26.2, R27.2
unnamed: C7.2, D19.2 (A), D20.1 (K), R28.1, R29.2
unnamed: D21.2 (A), R30.2, U4.1
unnamed: D21.1 (K), D22.1 (K), R31.1
unnamed: D23.2 (A), U4.7
unnamed: D23.1 (K), R34.2, R35.2, R36.2
unnamed: J6.1, J8.2
unnamed: J6.2, J8.4
unnamed: J6.3, J8.6
unnamed: J6.4, J8.8
unnamed: R2.1, R3.1, U1.2 (-)
unnamed: C2.1, R4.2, R6.2, U1.5 (+)
unnamed: R7.1, U1.6 (-)
unnamed: R11.1, R12.1, U2.2 (-)
unnamed: C4.1, R13.2, R15.2, U2.5 (+)
unnamed: R16.1, U2.6 (-)
unnamed: R20.1, R21.1, U3.2 (-)
unnamed: C6.1, R22.2, R24.2, U3.5 (+)
unnamed: R25.1, U3.6 (-)
unnamed: R29.1, R30.1, U4.2 (-)
unnamed: C8.1, R31.2, R33.2, U4.5 (+)
unnamed: R34.1, U4.6 (-)
unnamed: U5.11 (CLK), U7.10 (B4)
unnamed: U5.9 (Din), U7.12 (B2)
unnamed: U5.10 (Dout), U7.11 (B3)
unnamed: C21.2, U5.13 (Vref), U6.2 (Vout)
unnamed: U5.8 (~CS/SHDN), U7.13 (B1)
SCL: J5.2, J6.6
SDA: J5.3, J6.5
SPI MISO: J7.5, U7.4 (A3)
SPI MOSI: J7.4, U7.3 (A2)
SPI OE: J6.7, R37.1, U7.8 (OE)
SPI SCLK: J7.6, U7.5 (A4)
SPI nCS: J7.7, U7.2 (A1)

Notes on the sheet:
Seeed XIAO RP2040

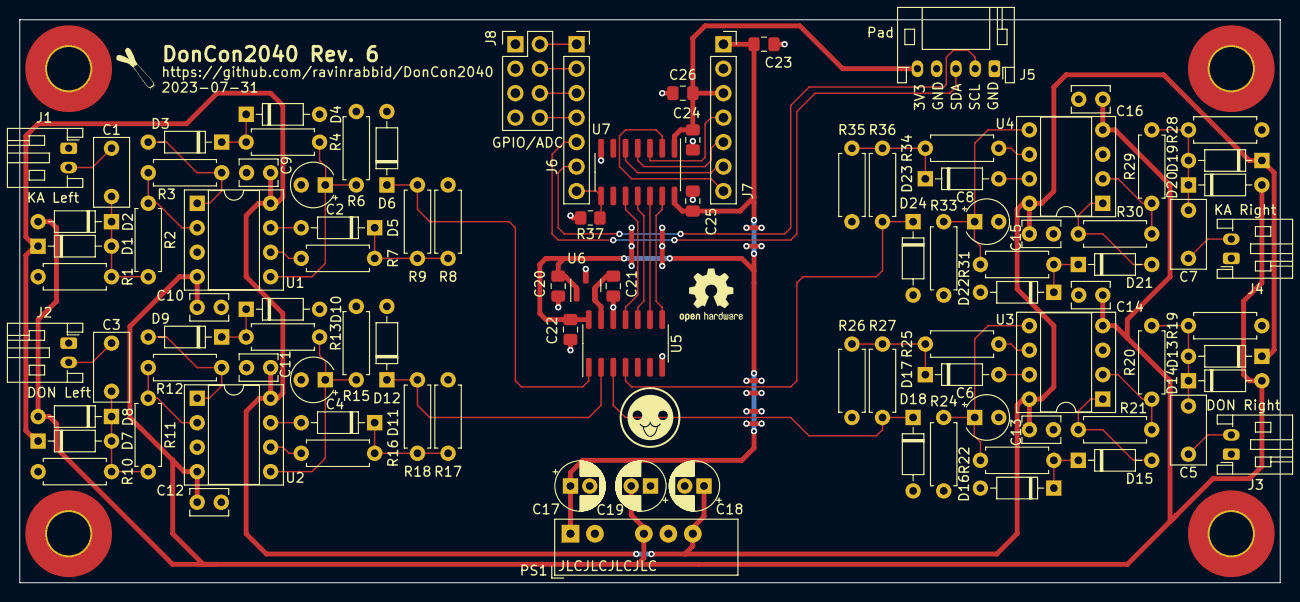
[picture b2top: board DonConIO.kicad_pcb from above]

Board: 2 copper layers, 130.8 x 58.4 mm, 105 parts (0 on the bottom side), 61 nets.

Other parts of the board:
REF01: OSHW-Logo2_7.3x6mm_SilkScreen
REF02: Donchan-Logo_6.3mm_Silkscreen
